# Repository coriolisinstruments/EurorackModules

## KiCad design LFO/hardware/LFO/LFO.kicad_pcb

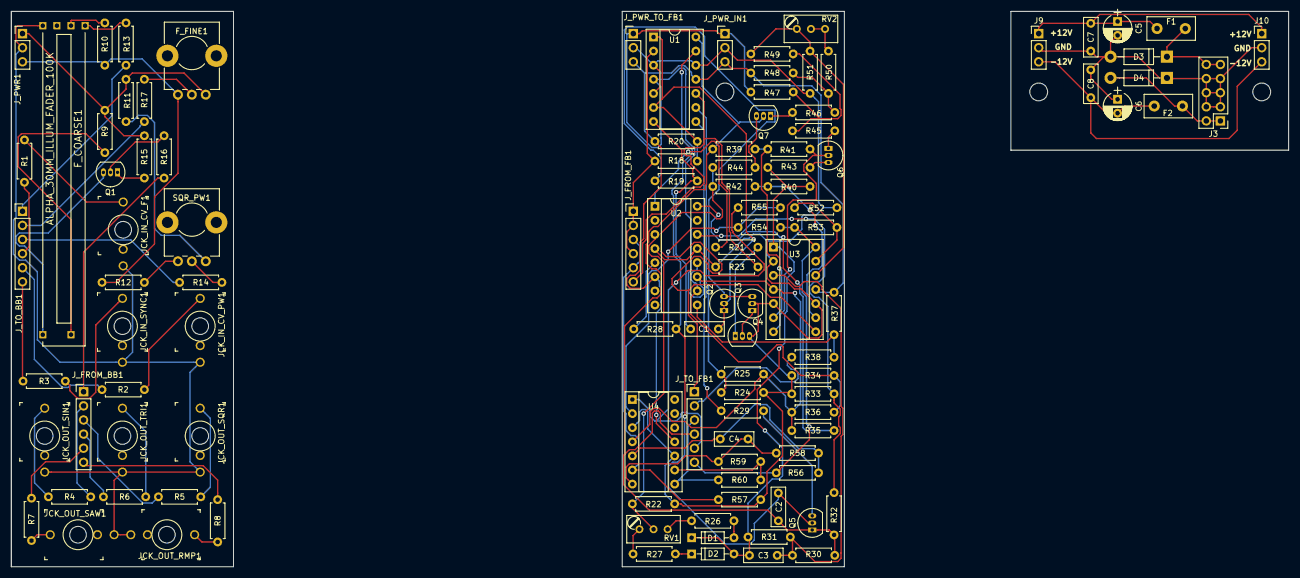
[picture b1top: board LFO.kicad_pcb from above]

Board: 2 copper layers, 230.0 x 100.0 mm, 111 parts (0 on the bottom side), 88 nets.

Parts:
C1: 100pF; C_Rect_L7.0mm_W2.5mm_P5.00mm
C2: 0.02uF; C_Rect_L7.0mm_W2.5mm_P5.00mm
C3, C4: 10pF; C_Rect_L7.0mm_W2.5mm_P5.00mm
C5, C6: 10uF; CP_Radial_D5.0mm_P2.50mm
C7, C8: 100nF; C_Rect_L7.0mm_W2.5mm_P5.00mm
D1, D2: 1N4148; D_DO-35_SOD27_P7.62mm_Horizontal
D3, D4: 1N4001; D_DO-41_SOD81_P10.16mm_Horizontal
F1, F2: Polyfuse; Fuse_TE5_Littlefuse-395Series
F_COARSE1: ALPHA_30MM_ILLUM_FADER_100K; ALPHA_ILL_FADER_45MM
F_FINE1: 100K; Potentiometer_Alps_RK09K_Horizontal
J3: Conn_02x05_Odd_Even; Pin_Header_Straight_2x05_Pitch2.54mm
J9, J10: Conn_01x03_Male; Pin_Header_Straight_1x03_Pitch2.54mm
JCK_IN_CV_F1: THONKICONNNEW; WQP-PJ301M-12_JACK
JCK_IN_CV_PW1: THONKICONNNEW; WQP-PJ301M-12_JACK
JCK_IN_SYNC1: THONKICONNNEW; WQP-PJ301M-12_JACK
JCK_OUT_RMP1: THONKICONNNEW; WQP-PJ301M-12_JACK
JCK_OUT_SAW1: THONKICONNNEW; WQP-PJ301M-12_JACK
JCK_OUT_SIN1: THONKICONNNEW; WQP-PJ301M-12_JACK
JCK_OUT_SQR1: THONKICONNNEW; WQP-PJ301M-12_JACK
JCK_OUT_TRI1: THONKICONNNEW; WQP-PJ301M-12_JACK
J_FROM_BB1: Conn_01x06_Male; Pin_Header_Straight_1x06_Pitch2.54mm
J_FROM_FB1: Conn_01x06_Female; Pin_Header_Straight_1x06_Pitch2.54mm
J_PWR1: Conn_01x03_Male; Pin_Header_Straight_1x03_Pitch2.54mm
J_PWR_IN1: Conn_01x03_Male; Pin_Header_Straight_1x03_Pitch2.54mm
J_PWR_TO_FB1: Conn_01x03_Female; Pin_Header_Straight_1x03_Pitch2.54mm
J_TO_BB1: Conn_01x06_Male; Pin_Header_Straight_1x06_Pitch2.54mm
J_TO_FB1: Conn_01x06_Female; Pin_Header_Straight_1x06_Pitch2.54mm
Q1, Q2, Q3: BC547; TO-92_Inline_Narrow_Oval
Q4: BC557; TO-92_Inline_Narrow_Oval
Q5, Q6, Q7: MPF102; TO-92_Inline_Narrow_Oval
R1, R3, R11, R12, R13, R16, R23, R25, R26, R27, R29, R53, R56: 100K; R_Axial_DIN0207_L6.3mm_D2.5mm_P7.62mm_Horizontal
R2, R14, R19, R21, R24, R45, R46, R49, R51, R54, R55, R60: 10K; R_Axial_DIN0207_L6.3mm_D2.5mm_P7.62mm_Horizontal
R4, R5, R6, R7, R8, R22, R38: 1K; R_Axial_DIN0207_L6.3mm_D2.5mm_P7.62mm_Horizontal
R9, R10, R59: 27K; R_Axial_DIN0207_L6.3mm_D2.5mm_P7.62mm_Horizontal
R15, R18, R33: 2K; R_Axial_DIN0207_L6.3mm_D2.5mm_P7.62mm_Horizontal
R17: 3M; R_Axial_DIN0207_L6.3mm_D2.5mm_P7.62mm_Horizontal
R20, R58: 4.7M; R_Axial_DIN0207_L6.3mm_D2.5mm_P7.62mm_Horizontal
R28: 39K; R_Axial_DIN0207_L6.3mm_D2.5mm_P7.62mm_Horizontal
R30: 120K; R_Axial_DIN0207_L6.3mm_D2.5mm_P7.62mm_Horizontal
R31: 270K; R_Axial_DIN0207_L6.3mm_D2.5mm_P7.62mm_Horizontal
R32: 110K; R_Axial_DIN0207_L6.3mm_D2.5mm_P7.62mm_Horizontal
R34: 180K; R_Axial_DIN0207_L6.3mm_D2.5mm_P7.62mm_Horizontal
R35: 680K; R_Axial_DIN0207_L6.3mm_D2.5mm_P7.62mm_Horizontal
R36: 2M; R_Axial_DIN0207_L6.3mm_D2.5mm_P7.62mm_Horizontal
R37: 4.7K; R_Axial_DIN0207_L6.3mm_D2.5mm_P7.62mm_Horizontal
R39, R41: 20K; R_Axial_DIN0207_L6.3mm_D2.5mm_P7.62mm_Horizontal
R40, R42, R52: 47K; R_Axial_DIN0207_L6.3mm_D2.5mm_P7.62mm_Horizontal
R43, R44: 30K; R_Axial_DIN0207_L6.3mm_D2.5mm_P7.62mm_Horizontal
R47, R48: 15K; R_Axial_DIN0207_L6.3mm_D2.5mm_P7.62mm_Horizontal
R50: 9.1K; R_Axial_DIN0207_L6.3mm_D2.5mm_P7.62mm_Horizontal
R57: 1M; R_Axial_DIN0207_L6.3mm_D2.5mm_P7.62mm_Horizontal
RV1: 100K; Potentiometer_Trimmer_Bourns_3296W
RV2: 2K; Potentiometer_Trimmer_Bourns_3296W
SQR_PW1: 100K; Potentiometer_Alps_RK09K_Horizontal
U1, U3, U4: TL074; DIP-14_W7.62mm_Socket
U2: LM13700; DIP-16_W7.62mm_Socket
screw: MountingHole_3.2mm_M3
screw#2, screw#3: MountingHole_3.2mm_M3

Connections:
+12V: J_PWR_IN1.1, J_PWR_TO_FB1.1, R25.2, R35.2, R36.2, R47.2, U1.4, U2.11, U3.4, U4.4
/LFO back board/-12V: J_PWR_IN1.3, J_PWR_TO_FB1.3, R20.1, R37.1, R48.1, U1.11, U2.6, U3.11, U4.11
/LFO back board/GND: J_PWR_IN1.2, J_PWR_TO_FB1.2, Q3.2, Q4.3, R22.1, R23.1, R24.1, R33.1, R34.1, R51.1, R52.2, R57.2, U1.3, U1.5, U1.12, U2.4, U2.13, U3.2, U3.5, U3.10, U4.3, U4.10
/LFO back board/Integrator/BIAS_INPUT: R21.1, U2.1
/LFO back board/Integrator/SQR_RAW: C3.1, D1.1, D2.2, R31.1, R40.2, R43.2, U3.1
/LFO back board/LED_RATE: J_TO_FB1.1, R42.1, R44.2, U3.8
/LFO back board/RMP: J_TO_FB1.6, R53.1, R54.2, R56.2, U3.14
/LFO back board/SAW: J_TO_FB1.5, R55.1, U4.1
/LFO back board/SIN: J_TO_FB1.2, R38.1
/LFO back board/SQR: J_TO_FB1.3, R60.1, U4.8
/LFO back board/TRI: C2.1, J_TO_FB1.4, Q5.1, Q7.2, R30.2, R32.2, R39.2, U1.14
/LFO back board/V_CF: J_FROM_FB1.1, J_FROM_FB1.2, J_FROM_FB1.4, R18.2, U1.2
/LFO back board/V_CV_PW: J_FROM_FB1.3, J_FROM_FB1.5, R57.1, U4.6
/LFO back board/V_SYNC: J_FROM_FB1.6, R23.2, U1.10
/LFO front board/+12V_FB: F_FINE1.1, J_PWR1.1, R9.1, R11.2, R15.2
/LFO front board/-12V_FB: F_FINE1.3, J_PWR1.3, R10.2, R12.2
/LFO front board/GND_FB: F_COARSE1.E, JCK_IN_CV_F1.P$3_SLEEVE, JCK_IN_CV_PW1.P$3_SLEEVE, JCK_IN_SYNC1.P$3_SLEEVE, JCK_OUT_RMP1.P$3_SLEEVE, JCK_OUT_SAW1.P$3_SLEEVE, JCK_OUT_SIN1.P$3_SLEEVE, JCK_OUT_SQR1.P$3_SLEEVE, JCK_OUT_TRI1.P$3_SLEEVE, J_PWR1.2
/LFO front board/LED_RATE_FB: J_FROM_BB1.1, R16.2
/LFO front board/RMP_FB: J_FROM_BB1.6, R8.1
/LFO front board/SAW_FB: J_FROM_BB1.5, R7.1
/LFO front board/SIN_FB: J_FROM_BB1.2, R4.1
/LFO front board/SQR_FB: J_FROM_BB1.3, R5.1
/LFO front board/TRI_FB: J_FROM_BB1.4, R6.1
/LFO front board/V_CF_FB: J_TO_BB1.1, R13.1
/LFO front board/V_CV_F_FB: J_TO_BB1.4, R1.1
/LFO front board/V_CV_PW_FB: J_TO_BB1.5, R2.1
/LFO front board/V_FF_FB: J_TO_BB1.2, R17.1
/LFO front board/V_PW_FB: J_TO_BB1.3, R14.2
/LFO front board/V_SYNC_FB: J_TO_BB1.6, R3.1
unnamed: C1.1, R19.2, U1.7
unnamed: C1.2, Q2.1, Q2.2, R18.1, R20.2, U1.1, U1.6
unnamed: C2.2, Q5.2, R28.1, U1.13
unnamed: C3.2, R30.1, R31.2, U3.3
unnamed: C4.1, R58.1, R59.2, U4.7
unnamed: C4.2, R56.1, R58.2, U4.5
unnamed: C5.1, C7.1, F1.1, J9.1, J10.1
unnamed: C5.2, C6.1, C7.2, C8.1, D3.2, D4.1, J3.3, J3.4, J3.5, J3.6, J3.7, J3.8, J9.2, J10.2
unnamed: C6.2, C8.2, F2.2, J9.3, J10.3
unnamed: D1.2, R26.1
unnamed: D2.1, R27.1
unnamed: D3.1, F1.2, J3.9, J3.10
unnamed: D4.2, F2.1, J3.1, J3.2
unnamed: F_COARSE1.1, R10.1
unnamed: F_COARSE1.2, R13.2
unnamed: F_COARSE1.3, R9.2
unnamed: F_COARSE1.B, Q1.3
unnamed: F_FINE1.2, R17.2
unnamed: JCK_IN_CV_F1.P$1_TIP, R1.2
unnamed: JCK_IN_CV_PW1.P$1_TIP, R2.2
unnamed: JCK_IN_SYNC1.P$1_TIP, R3.2
unnamed: JCK_OUT_RMP1.P$1_TIP, R8.2
unnamed: JCK_OUT_SAW1.P$1_TIP, R7.2
unnamed: JCK_OUT_SIN1.P$1_TIP, R4.2
unnamed: JCK_OUT_SQR1.P$1_TIP, R5.2
unnamed: JCK_OUT_TRI1.P$1_TIP, R6.2
unnamed: Q1.1, R15.1
unnamed: Q1.2, R16.1
unnamed: Q2.3, Q3.3, R19.1
unnamed: Q3.1, Q4.2
unnamed: Q4.1, R21.2
unnamed: Q5.3, R29.2
unnamed: Q6.1, R45.2
unnamed: Q6.2, R41.1, U3.7
unnamed: Q6.3, R43.1
unnamed: Q7.1, R46.2
unnamed: Q7.3, R44.1
unnamed: R11.1, SQR_PW1.1
unnamed: R12.1, SQR_PW1.3
unnamed: R14.1, SQR_PW1.2
unnamed: R22.2, RV1.2, U2.3
unnamed: R24.2, R25.1, U1.9
unnamed: R26.2, RV1.3
unnamed: R27.2, RV1.1
unnamed: R28.2, U2.5
unnamed: R29.1, U1.8
unnamed: R32.1, R33.2, U2.14
unnamed: R34.2, R36.1, U2.10, U2.12
unnamed: R35.1, U2.16
unnamed: R37.2, R38.2, U2.9
unnamed: R39.1, R41.2, U3.6
unnamed: R40.1, R42.2, U3.9
unnamed: R45.1, R47.1, R49.2
unnamed: R46.1, R48.2, R50.2
unnamed: R49.1, R51.2, RV2.1, U3.12
unnamed: R50.1, RV2.2, RV2.3
unnamed: R52.1, R53.2, U3.13
unnamed: R54.1, R55.2, U4.2
unnamed: R59.1, R60.2, U4.9

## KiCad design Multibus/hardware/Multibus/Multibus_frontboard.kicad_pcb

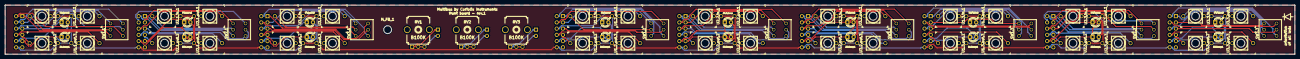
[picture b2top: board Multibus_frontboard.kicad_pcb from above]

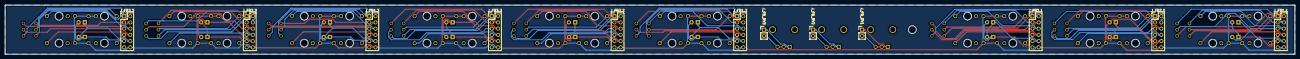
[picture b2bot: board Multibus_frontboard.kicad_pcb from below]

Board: 2 copper layers, 526.0 x 20.0 mm, 79 parts (12 on the bottom side), 106 nets.

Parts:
D1.1.neg.1, D1.1.pos.1, D1.2.neg.1, D1.2.pos.1, D1.3.neg.1, D1.3.pos.1, D2.1.neg.1, D2.1.pos.1, D2.2.neg.1, D2.2.pos.1, D2.3.neg.1, D2.3.pos.1, D3.1.neg.1, D3.1.pos.1, D3.2.neg.1, D3.2.pos.1, D3.3.neg.1, D3.3.pos.1: LED; LED_D3.0mm_smalltext
H_FB_1: MountingHole; MountingHole_3.2mm_M3
J_FB1.1, J_FB1.2, J_FB1.3, J_FB2.1, J_FB2.2, J_FB2.3, J_FB3.1, J_FB3.2, J_FB3.3: Conn_01x12; PinHeader_2x06_P2.54mm_Vertical
J_FB_RV1, J_FB_RV2, J_FB_RV3: Conn_01x02; PinHeader_1x02_P2.54mm_Vertical
RV1, RV2, RV3: B100K; 9MM_SNAP-IN_POT
SW1.1, SW1.2, SW1.3, SW2.1, SW2.2, SW2.3, SW3.1, SW3.2, SW3.3: SW_DPDT_x2; SUBMINI_TOGGLE_DPDT
U1.1.in.1, U1.1.out.1, U1.1.out.2, U1.1.out.3, U1.2.in.1, U1.2.out.1, U1.2.out.2, U1.2.out.3, U1.3.in.1, U1.3.out.1, U1.3.out.2, U1.3.out.3, U2.1.in.1, U2.1.out.1, U2.1.out.2, U2.1.out.3, U2.2.in.1, U2.2.out.1, U2.2.out.2, U2.2.out.3, U2.3.in.1, U2.3.out.1, U2.3.out.2, U2.3.out.3, U3.1.in.1, U3.1.out.1, U3.1.out.2, U3.1.out.3, U3.2.in.1, U3.2.out.1, U3.2.out.2, U3.2.out.3, U3.3.in.1, U3.3.out.1, U3.3.out.2, U3.3.out.3: THONKICONNNEW; MusicThingModular-WQP-PJ301M-12_JACK

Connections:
/cv_bus1/fb.1.1.leds.in: D1.1.neg.1.1, D1.1.pos.1.2, J_FB1.1.9
/cv_bus1/fb.1.1.leds.out: D1.1.neg.1.2, D1.1.pos.1.1, J_FB1.1.10
/cv_bus1/fb.1.1.out.1: J_FB1.1.6, U1.1.out.1.P$1_TIP
/cv_bus1/fb.1.1.out.2: J_FB1.1.7, U1.1.out.2.P$1_TIP
/cv_bus1/fb.1.1.out.3: J_FB1.1.8, U1.1.out.3.P$1_TIP
/cv_bus1/fb.1.2.leds.in: D1.2.neg.1.1, D1.2.pos.1.2, J_FB1.2.9
/cv_bus1/fb.1.2.leds.out: D1.2.neg.1.2, D1.2.pos.1.1, J_FB1.2.10
/cv_bus1/fb.1.2.out.1: J_FB1.2.6, U1.2.out.1.P$1_TIP
/cv_bus1/fb.1.2.out.2: J_FB1.2.7, U1.2.out.2.P$1_TIP
/cv_bus1/fb.1.2.out.3: J_FB1.2.8, U1.2.out.3.P$1_TIP
/cv_bus1/fb.1.3.leds.in: D1.3.neg.1.1, D1.3.pos.1.2, J_FB1.3.9
/cv_bus1/fb.1.3.leds.out: D1.3.neg.1.2, D1.3.pos.1.1, J_FB1.3.10
/cv_bus1/fb.1.3.out.1: J_FB1.3.6, U1.3.out.1.P$1_TIP
/cv_bus1/fb.1.3.out.2: J_FB1.3.7, U1.3.out.2.P$1_TIP
/cv_bus1/fb.1.3.out.3: J_FB1.3.8, U1.3.out.3.P$1_TIP
/cv_bus1/fb.bus1.1.in: J_FB1.1.3, SW1.1.3
/cv_bus1/fb.bus1.1.out: J_FB1.1.4, SW1.1.6
/cv_bus1/fb.bus1.2.in: J_FB1.2.3, SW1.2.3
/cv_bus1/fb.bus1.2.out: J_FB1.2.4, SW1.2.6
/cv_bus1/fb.bus1.3.in: J_FB1.3.3, SW1.3.3
/cv_bus1/fb.bus1.3.out: J_FB1.3.4, SW1.3.6
/cv_bus1/fb.rv1.in: J_FB_RV1.1, RV1.1
/cv_bus1/fb.rv1.out: J_FB_RV1.2, RV1.2, RV1.3
/cv_bus1/fb.sel.1.1.out: J_FB1.1.5, SW1.1.5
/cv_bus1/fb.sel.1.2.out: J_FB1.2.5, SW1.2.5
/cv_bus1/fb.sel.1.3.out: J_FB1.3.5, SW1.3.5
/cv_bus1/fb.solo1.1.in: J_FB1.1.1, SW1.1.1
/cv_bus1/fb.solo1.1.out: J_FB1.1.2, SW1.1.4
/cv_bus1/fb.solo1.2.in: J_FB1.2.1, SW1.2.1
/cv_bus1/fb.solo1.2.out: J_FB1.2.2, SW1.2.4
/cv_bus1/fb.solo1.3.in: J_FB1.3.1, SW1.3.1
/cv_bus1/fb.solo1.3.out: J_FB1.3.2, SW1.3.4
/cv_bus2/fb.2.1.leds.in: D2.1.neg.1.1, D2.1.pos.1.2, J_FB2.1.9
/cv_bus2/fb.2.1.leds.out: D2.1.neg.1.2, D2.1.pos.1.1, J_FB2.1.10
/cv_bus2/fb.2.1.out.1: J_FB2.1.6, U2.1.out.1.P$1_TIP
/cv_bus2/fb.2.1.out.2: J_FB2.1.7, U2.1.out.2.P$1_TIP
/cv_bus2/fb.2.1.out.3: J_FB2.1.8, U2.1.out.3.P$1_TIP
/cv_bus2/fb.2.2.leds.in: D2.2.neg.1.1, D2.2.pos.1.2, J_FB2.2.9
/cv_bus2/fb.2.2.leds.out: D2.2.neg.1.2, D2.2.pos.1.1, J_FB2.2.10
/cv_bus2/fb.2.2.out.1: J_FB2.2.6, U2.2.out.1.P$1_TIP
/cv_bus2/fb.2.2.out.2: J_FB2.2.7, U2.2.out.2.P$1_TIP
/cv_bus2/fb.2.2.out.3: J_FB2.2.8, U2.2.out.3.P$1_TIP
/cv_bus2/fb.2.3.leds.in: D2.3.neg.1.1, D2.3.pos.1.2, J_FB2.3.9
/cv_bus2/fb.2.3.leds.out: D2.3.neg.1.2, D2.3.pos.1.1, J_FB2.3.10
/cv_bus2/fb.2.3.out.1: J_FB2.3.6, U2.3.out.1.P$1_TIP
/cv_bus2/fb.2.3.out.2: J_FB2.3.7, U2.3.out.2.P$1_TIP
/cv_bus2/fb.2.3.out.3: J_FB2.3.8, U2.3.out.3.P$1_TIP
/cv_bus2/fb.bus2.1.in: J_FB2.1.3, SW2.1.3
/cv_bus2/fb.bus2.1.out: J_FB2.1.4, SW2.1.6
/cv_bus2/fb.bus2.2.in: J_FB2.2.3, SW2.2.3
/cv_bus2/fb.bus2.2.out: J_FB2.2.4, SW2.2.6
/cv_bus2/fb.bus2.3.in: J_FB2.3.3, SW2.3.3
/cv_bus2/fb.bus2.3.out: J_FB2.3.4, SW2.3.6
/cv_bus2/fb.rv2.in: J_FB_RV2.1, RV2.1
/cv_bus2/fb.rv2.out: J_FB_RV2.2, RV2.2, RV2.3
/cv_bus2/fb.sel.2.1.out: J_FB2.1.5, SW2.1.5
/cv_bus2/fb.sel.2.2.out: J_FB2.2.5, SW2.2.5
/cv_bus2/fb.sel.2.3.out: J_FB2.3.5, SW2.3.5
/cv_bus2/fb.solo2.1.in: J_FB2.1.1, SW2.1.1
/cv_bus2/fb.solo2.1.out: J_FB2.1.2, SW2.1.4
/cv_bus2/fb.solo2.2.in: J_FB2.2.1, SW2.2.1
/cv_bus2/fb.solo2.2.out: J_FB2.2.2, SW2.2.4
/cv_bus2/fb.solo2.3.in: J_FB2.3.1, SW2.3.1
/cv_bus2/fb.solo2.3.out: J_FB2.3.2, SW2.3.4
/cv_bus3/fb.3.1.leds.in: D3.1.neg.1.1, D3.1.pos.1.2, J_FB3.1.9
/cv_bus3/fb.3.1.leds.out: D3.1.neg.1.2, D3.1.pos.1.1, J_FB3.1.10
/cv_bus3/fb.3.1.out.1: J_FB3.1.6, U3.1.out.1.P$1_TIP
/cv_bus3/fb.3.1.out.2: J_FB3.1.7, U3.1.out.2.P$1_TIP
/cv_bus3/fb.3.1.out.3: J_FB3.1.8, U3.1.out.3.P$1_TIP
/cv_bus3/fb.3.2.leds.in: D3.2.neg.1.1, D3.2.pos.1.2, J_FB3.2.9
/cv_bus3/fb.3.2.leds.out: D3.2.neg.1.2, D3.2.pos.1.1, J_FB3.2.10
/cv_bus3/fb.3.2.out.1: J_FB3.2.6, U3.2.out.1.P$1_TIP
/cv_bus3/fb.3.2.out.2: J_FB3.2.7, U3.2.out.2.P$1_TIP
/cv_bus3/fb.3.2.out.3: J_FB3.2.8, U3.2.out.3.P$1_TIP
/cv_bus3/fb.3.3.leds.in: D3.3.neg.1.1, D3.3.pos.1.2, J_FB3.3.9
/cv_bus3/fb.3.3.leds.out: D3.3.neg.1.2, D3.3.pos.1.1, J_FB3.3.10
/cv_bus3/fb.3.3.out.1: J_FB3.3.6, U3.3.out.1.P$1_TIP
/cv_bus3/fb.3.3.out.2: J_FB3.3.7, U3.3.out.2.P$1_TIP
/cv_bus3/fb.3.3.out.3: J_FB3.3.8, U3.3.out.3.P$1_TIP
/cv_bus3/fb.bus3.1.in: J_FB3.1.3, SW3.1.3
/cv_bus3/fb.bus3.1.out: J_FB3.1.4, SW3.1.6
/cv_bus3/fb.bus3.2.in: J_FB3.2.3, SW3.2.3
/cv_bus3/fb.bus3.2.out: J_FB3.2.4, SW3.2.6
/cv_bus3/fb.bus3.3.in: J_FB3.3.3, SW3.3.3
/cv_bus3/fb.bus3.3.out: J_FB3.3.4, SW3.3.6
/cv_bus3/fb.rv3.in: J_FB_RV3.1, RV3.1
/cv_bus3/fb.rv3.out: J_FB_RV3.2, RV3.2, RV3.3
/cv_bus3/fb.sel.3.1.out: J_FB3.1.5, SW3.1.5
/cv_bus3/fb.sel.3.2.out: J_FB3.2.5, SW3.2.5
/cv_bus3/fb.sel.3.3.out: J_FB3.3.5, SW3.3.5
/cv_bus3/fb.solo3.1.in: J_FB3.1.1, SW3.1.1
/cv_bus3/fb.solo3.1.out: J_FB3.1.2, SW3.1.4
/cv_bus3/fb.solo3.2.in: J_FB3.2.1, SW3.2.1
/cv_bus3/fb.solo3.2.out: J_FB3.2.2, SW3.2.4
/cv_bus3/fb.solo3.3.in: J_FB3.3.1, SW3.3.1
/cv_bus3/fb.solo3.3.out: J_FB3.3.2, SW3.3.4
FB_GND: J_FB1.1.12, J_FB1.2.12, J_FB1.3.12, J_FB2.1.12, J_FB2.2.12, J_FB2.3.12, J_FB3.1.12, J_FB3.2.12, J_FB3.3.12, U1.1.in.1.P$2_SWITCH, U1.1.in.1.P$3_SLEEVE, U1.1.out.1.P$3_SLEEVE, U1.1.out.2.P$3_SLEEVE, U1.1.out.3.P$3_SLEEVE, U1.2.in.1.P$2_SWITCH, U1.2.in.1.P$3_SLEEVE, U1.2.out.1.P$3_SLEEVE, U1.2.out.2.P$3_SLEEVE, U1.2.out.3.P$3_SLEEVE, U1.3.in.1.P$2_SWITCH, U1.3.in.1.P$3_SLEEVE, U1.3.out.1.P$3_SLEEVE, U1.3.out.2.P$3_SLEEVE, U1.3.out.3.P$3_SLEEVE, U2.1.in.1.P$2_SWITCH, U2.1.in.1.P$3_SLEEVE, U2.1.out.1.P$3_SLEEVE, U2.1.out.2.P$3_SLEEVE, U2.1.out.3.P$3_SLEEVE, U2.2.in.1.P$2_SWITCH, U2.2.in.1.P$3_SLEEVE, U2.2.out.1.P$3_SLEEVE, U2.2.out.2.P$3_SLEEVE, U2.2.out.3.P$3_SLEEVE, U2.3.in.1.P$2_SWITCH, U2.3.in.1.P$3_SLEEVE, U2.3.out.1.P$3_SLEEVE, U2.3.out.2.P$3_SLEEVE, U2.3.out.3.P$3_SLEEVE, U3.1.in.1.P$2_SWITCH, U3.1.in.1.P$3_SLEEVE, U3.1.out.1.P$3_SLEEVE, U3.1.out.2.P$3_SLEEVE, U3.1.out.3.P$3_SLEEVE, U3.2.in.1.P$2_SWITCH, U3.2.in.1.P$3_SLEEVE, U3.2.out.1.P$3_SLEEVE, U3.2.out.2.P$3_SLEEVE, U3.2.out.3.P$3_SLEEVE, U3.3.in.1.P$2_SWITCH, U3.3.in.1.P$3_SLEEVE, U3.3.out.1.P$3_SLEEVE, U3.3.out.2.P$3_SLEEVE, U3.3.out.3.P$3_SLEEVE
unnamed: SW1.1.2, U1.1.in.1.P$1_TIP
unnamed: SW1.2.2, U1.2.in.1.P$1_TIP
unnamed: SW1.3.2, U1.3.in.1.P$1_TIP
unnamed: SW2.1.2, U2.1.in.1.P$1_TIP
unnamed: SW2.2.2, U2.2.in.1.P$1_TIP
unnamed: SW2.3.2, U2.3.in.1.P$1_TIP
unnamed: SW3.1.2, U3.1.in.1.P$1_TIP
unnamed: SW3.2.2, U3.2.in.1.P$1_TIP
unnamed: SW3.3.2, U3.3.in.1.P$1_TIP

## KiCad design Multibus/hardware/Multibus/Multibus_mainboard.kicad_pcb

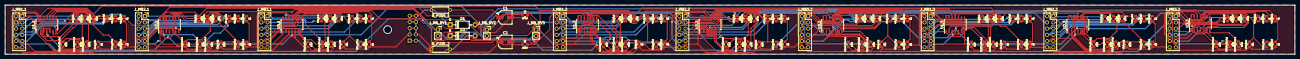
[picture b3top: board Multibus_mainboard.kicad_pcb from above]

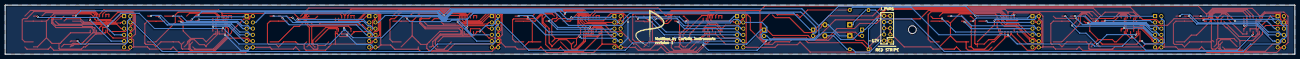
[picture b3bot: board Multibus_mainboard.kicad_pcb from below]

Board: 2 copper layers, 526.0 x 20.0 mm, 140 parts (2 on the bottom side), 125 nets.

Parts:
C1, C2: 10uF (25V); CP_Elec_5x5.8
C1.1.feedback.1, C1.2.feedback.1, C1.3.feedback.1, C2.1.feedback.1, C2.2.feedback.1, C2.3.feedback.1, C3.1.feedback.1, C3.2.feedback.1, C3.3.feedback.1: 10pF; C_0805_2012Metric_Pad1.15x1.40mm_HandSolder_smalltext
C3, C4: 100nF; C_0805_2012Metric_Pad1.15x1.40mm_HandSolder_smalltext
D1, D2: IN4001; D_DO-41_SOD81_P10.16mm_Horizontal
H_MB_2: MountingHole; MountingHole_3.2mm_M3
J_MB1.1, J_MB1.2, J_MB1.3, J_MB2.1, J_MB2.2, J_MB2.3, J_MB3.1, J_MB3.2, J_MB3.3: Conn_01x12; PinSocket_2x06_P2.54mm_Vertical
J_MB_RV1, J_MB_RV2, J_MB_RV3: Conn_01x02; PinSocket_1x02_P2.54mm_Vertical
J_PWR1: Conn_02x05_Odd_Even; PinHeader_2x05_P2.54mm_Vertical
MK1: CoriolisLogo; art_Coriolis_logo_fsilk
R1.1.feedback.1, R1.1.feedback.2, R1.1.in.1, R1.1.in.2, R1.1.in.3, R1.2.feedback.1, R1.2.feedback.2, R1.2.in.1, R1.2.in.2, R1.2.in.3, R1.3.feedback.1, R1.3.feedback.2, R1.3.in.1, R1.3.in.2, R1.3.in.3, R2.1.feedback.1, R2.1.feedback.2, R2.1.in.1, R2.1.in.2, R2.1.in.3, R2.2.feedback.1, R2.2.feedback.2, R2.2.in.1, R2.2.in.2, R2.2.in.3, R2.3.feedback.1, R2.3.feedback.2, R2.3.in.1, R2.3.in.2, R2.3.in.3, R3.1.feedback.1, R3.1.feedback.2, R3.1.in.1, R3.1.in.2, R3.1.in.3, R3.2.feedback.1, R3.2.feedback.2, R3.2.in.1, R3.2.in.2, R3.2.in.3, R3.3.feedback.1, R3.3.feedback.2, R3.3.in.1, R3.3.in.2, R3.3.in.3: 100K; R_0805_2012Metric_Pad1.15x1.40mm_HandSolder_smalltext
R1.1.led.1, R1.1.split.2, R1.2.led.1, R1.2.split.2, R1.3.led.1, R1.3.split.2, R2.1.split.2, R2.2.split.2, R2.3.split.2, R3.1.split.2, R3.2.split.2, R3.3.split.2: 1K; R_0805_2012Metric_Pad1.15x1.40mm_HandSolder_smalltext
R1.1.out.1, R1.1.out.2, R1.1.out.3, R1.2.out.1, R1.2.out.2, R1.2.out.3, R1.3.out.1, R1.3.out.2, R1.3.out.3, R2.1.out.1, R2.1.out.2, R2.1.out.3, R2.2.out.1, R2.2.out.2, R2.2.out.3, R2.3.out.1, R2.3.out.2, R2.3.out.3, R3.1.out.1, R3.1.out.2, R3.1.out.3, R3.2.out.1, R3.2.out.2, R3.2.out.3, R3.3.out.1, R3.3.out.2, R3.3.out.3: 51; R_0805_2012Metric_Pad1.15x1.40mm_HandSolder_smalltext
R1.1.split.1, R1.2.split.1, R1.3.split.1, R2.1.split.1, R2.2.split.1, R2.3.split.1, R3.1.split.1, R3.2.split.1, R3.3.split.1: 10K; R_0805_2012Metric_Pad1.15x1.40mm_HandSolder_smalltext
R2.1.led.1, R2.2.led.1, R2.3.led.1: 510R; R_0805_2012Metric_Pad1.15x1.40mm_HandSolder_smalltext
R3.1.led.1, R3.2.led.1, R3.3.led.1: 5K1; R_0805_2012Metric_Pad1.15x1.40mm_HandSolder_smalltext
R_FUSE_1, R_FUSE_2: 10R; R_Axial_DIN0207_L6.3mm_D2.5mm_P7.62mm_Horizontal
U1.1, U1.2, U1.3, U2.1, U2.2, U2.3, U3.1, U3.2, U3.3: TL074; SOIC-14_3.9x8.7mm_P1.27mm

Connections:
+12V: C1.1, C3.1, R_FUSE_1.1, U1.1.4, U1.2.4, U1.3.4, U2.1.4, U2.2.4, U2.3.4, U3.1.4, U3.2.4, U3.3.4
-12V: C2.2, C4.2, R_FUSE_2.1, U1.1.11, U1.2.11, U1.3.11, U2.1.11, U2.2.11, U2.3.11, U3.1.11, U3.2.11, U3.3.11
/cv_bus1/1.1.leds.in: J_MB1.1.9, U1.1.8
/cv_bus1/1.1.leds.out: C1.1.feedback.1.1, J_MB1.1.10, R1.1.feedback.2.2, R1.1.led.1.2, R1.1.out.1.1, R1.1.out.2.1, R1.1.out.3.1, R1.1.split.1.1, U1.1.7, U1.1.9
/cv_bus1/1.1.out.1: J_MB1.1.6, R1.1.out.1.2
/cv_bus1/1.1.out.2: J_MB1.1.7, R1.1.out.2.2
/cv_bus1/1.1.out.3: J_MB1.1.8, R1.1.out.3.2
/cv_bus1/1.2.leds.in: J_MB1.2.9, U1.2.8
/cv_bus1/1.2.leds.out: C1.2.feedback.1.1, J_MB1.2.10, R1.2.feedback.2.2, R1.2.led.1.2, R1.2.out.1.1, R1.2.out.2.1, R1.2.out.3.1, R1.2.split.1.1, U1.2.7, U1.2.9
/cv_bus1/1.2.out.1: J_MB1.2.6, R1.2.out.1.2
/cv_bus1/1.2.out.2: J_MB1.2.7, R1.2.out.2.2
/cv_bus1/1.2.out.3: J_MB1.2.8, R1.2.out.3.2
/cv_bus1/1.3.leds.in: J_MB1.3.9, U1.3.8
/cv_bus1/1.3.leds.out: C1.3.feedback.1.1, J_MB1.3.10, R1.3.feedback.2.2, R1.3.led.1.2, R1.3.out.1.1, R1.3.out.2.1, R1.3.out.3.1, R1.3.split.1.1, U1.3.7, U1.3.9
/cv_bus1/1.3.out.1: J_MB1.3.6, R1.3.out.1.2
/cv_bus1/1.3.out.2: J_MB1.3.7, R1.3.out.2.2
/cv_bus1/1.3.out.3: J_MB1.3.8, R1.3.out.3.2
/cv_bus1/bus1.1.in: J_MB1.1.3, R1.1.in.3.1
/cv_bus1/bus1.2.in: J_MB1.2.3, R1.2.in.3.1
/cv_bus1/bus1.3.in: J_MB1.3.3, R1.3.in.3.1
/cv_bus1/bus1.out: J_MB1.1.4, J_MB1.2.4, J_MB1.3.4, J_MB_RV1.1, U1.1.14
/cv_bus1/rv1.out: J_MB_RV1.2, R1.1.in.3.2, R1.2.in.3.2, R1.3.in.3.2, U1.1.13
/cv_bus1/sel.1.1.out: J_MB1.1.5, R1.1.in.2.1
/cv_bus1/sel.1.2.out: J_MB1.2.5, R1.2.in.2.1
/cv_bus1/sel.1.3.out: J_MB1.3.5, R1.3.in.2.1
/cv_bus1/solo1.1.in: J_MB1.1.1, R1.1.in.1.1
/cv_bus1/solo1.1.out: J_MB1.1.2, R1.1.feedback.1.2, U1.1.1
/cv_bus1/solo1.2.in: J_MB1.2.1, R1.2.in.1.1
/cv_bus1/solo1.2.out: J_MB1.2.2, R1.2.feedback.1.2, U1.2.1
/cv_bus1/solo1.3.in: J_MB1.3.1, R1.3.in.1.1
/cv_bus1/solo1.3.out: J_MB1.3.2, R1.3.feedback.1.2, U1.3.1
/cv_bus2/2.1.leds.in: J_MB2.1.9, U2.1.8
/cv_bus2/2.1.leds.out: C2.1.feedback.1.1, J_MB2.1.10, R2.1.feedback.2.2, R2.1.led.1.2, R2.1.out.1.1, R2.1.out.2.1, R2.1.out.3.1, R2.1.split.1.1, U2.1.7, U2.1.9
/cv_bus2/2.1.out.1: J_MB2.1.6, R2.1.out.1.2
/cv_bus2/2.1.out.2: J_MB2.1.7, R2.1.out.2.2
/cv_bus2/2.1.out.3: J_MB2.1.8, R2.1.out.3.2
/cv_bus2/2.2.leds.in: J_MB2.2.9, U2.2.8
/cv_bus2/2.2.leds.out: C2.2.feedback.1.1, J_MB2.2.10, R2.2.feedback.2.2, R2.2.led.1.2, R2.2.out.1.1, R2.2.out.2.1, R2.2.out.3.1, R2.2.split.1.1, U2.2.7, U2.2.9
/cv_bus2/2.2.out.1: J_MB2.2.6, R2.2.out.1.2
/cv_bus2/2.2.out.2: J_MB2.2.7, R2.2.out.2.2
/cv_bus2/2.2.out.3: J_MB2.2.8, R2.2.out.3.2
/cv_bus2/2.3.leds.in: J_MB2.3.9, U2.3.8
/cv_bus2/2.3.leds.out: C2.3.feedback.1.1, J_MB2.3.10, R2.3.feedback.2.2, R2.3.led.1.2, R2.3.out.1.1, R2.3.out.2.1, R2.3.out.3.1, R2.3.split.1.1, U2.3.7, U2.3.9
/cv_bus2/2.3.out.1: J_MB2.3.6, R2.3.out.1.2
/cv_bus2/2.3.out.2: J_MB2.3.7, R2.3.out.2.2
/cv_bus2/2.3.out.3: J_MB2.3.8, R2.3.out.3.2
/cv_bus2/bus2.1.in: J_MB2.1.3, R2.1.in.1.1
/cv_bus2/bus2.2.in: J_MB2.2.3, R2.2.in.1.1
/cv_bus2/bus2.3.in: J_MB2.3.3, R2.3.in.1.1
/cv_bus2/bus2.out: J_MB2.1.4, J_MB2.2.4, J_MB2.3.4, J_MB_RV2.1, U2.1.14
/cv_bus2/rv2.out: J_MB_RV2.2, R2.1.in.1.2, R2.2.in.1.2, R2.3.in.1.2, U2.1.13
/cv_bus2/sel.2.1.out: J_MB2.1.5, R2.1.in.3.1
/cv_bus2/sel.2.2.out: J_MB2.2.5, R2.2.in.3.1
/cv_bus2/sel.2.3.out: J_MB2.3.5, R2.3.in.3.1
/cv_bus2/solo2.1.in: J_MB2.1.1, R2.1.in.2.1
/cv_bus2/solo2.1.out: J_MB2.1.2, R2.1.feedback.1.2, U2.1.1
/cv_bus2/solo2.2.in: J_MB2.2.1, R2.2.in.2.1
/cv_bus2/solo2.2.out: J_MB2.2.2, R2.2.feedback.1.2, U2.2.1
/cv_bus2/solo2.3.in: J_MB2.3.1, R2.3.in.2.1
/cv_bus2/solo2.3.out: J_MB2.3.2, R2.3.feedback.1.2, U2.3.1
/cv_bus3/3.1.leds.in: J_MB3.1.9, U3.1.8
/cv_bus3/3.1.leds.out: C3.1.feedback.1.1, J_MB3.1.10, R3.1.feedback.2.2, R3.1.led.1.2, R3.1.out.1.1, R3.1.out.2.1, R3.1.out.3.1, R3.1.split.1.1, U3.1.7, U3.1.9
/cv_bus3/3.1.out.1: J_MB3.1.6, R3.1.out.1.2
/cv_bus3/3.1.out.2: J_MB3.1.7, R3.1.out.2.2
/cv_bus3/3.1.out.3: J_MB3.1.8, R3.1.out.3.2
/cv_bus3/3.2.leds.in: J_MB3.2.9, U3.2.8
/cv_bus3/3.2.leds.out: C3.2.feedback.1.1, J_MB3.2.10, R3.2.feedback.2.2, R3.2.led.1.2, R3.2.out.1.1, R3.2.out.2.1, R3.2.out.3.1, R3.2.split.1.1, U3.2.7, U3.2.9
/cv_bus3/3.2.out.1: J_MB3.2.6, R3.2.out.1.2
/cv_bus3/3.2.out.2: J_MB3.2.7, R3.2.out.2.2
/cv_bus3/3.2.out.3: J_MB3.2.8, R3.2.out.3.2
/cv_bus3/3.3.leds.in: J_MB3.3.9, U3.3.8
/cv_bus3/3.3.leds.out: C3.3.feedback.1.1, J_MB3.3.10, R3.3.feedback.2.2, R3.3.led.1.2, R3.3.out.1.1, R3.3.out.2.1, R3.3.out.3.1, R3.3.split.1.1, U3.3.7, U3.3.9
/cv_bus3/3.3.out.1: J_MB3.3.6, R3.3.out.1.2
/cv_bus3/3.3.out.2: J_MB3.3.7, R3.3.out.2.2
/cv_bus3/3.3.out.3: J_MB3.3.8, R3.3.out.3.2
/cv_bus3/bus3.1.in: J_MB3.1.3, R3.1.in.1.1
/cv_bus3/bus3.2.in: J_MB3.2.3, R3.2.in.1.1
/cv_bus3/bus3.3.in: J_MB3.3.3, R3.3.in.1.1
/cv_bus3/bus3.out: J_MB3.1.4, J_MB3.2.4, J_MB3.3.4, J_MB_RV3.1, U3.1.14
/cv_bus3/rv3.out: J_MB_RV3.2, R3.1.in.1.2, R3.2.in.1.2, R3.3.in.1.2, U3.1.13
/cv_bus3/sel.3.1.out: J_MB3.1.5, R3.1.in.3.1
/cv_bus3/sel.3.2.out: J_MB3.2.5, R3.2.in.3.1
/cv_bus3/sel.3.3.out: J_MB3.3.5, R3.3.in.3.1
/cv_bus3/solo3.1.in: J_MB3.1.1, R3.1.in.2.1
/cv_bus3/solo3.1.out: J_MB3.1.2, R3.1.feedback.1.2, U3.1.1
/cv_bus3/solo3.2.in: J_MB3.2.1, R3.2.in.2.1
/cv_bus3/solo3.2.out: J_MB3.2.2, R3.2.feedback.1.2, U3.2.1
/cv_bus3/solo3.3.in: J_MB3.3.1, R3.3.in.2.1
/cv_bus3/solo3.3.out: J_MB3.3.2, R3.3.feedback.1.2, U3.3.1
GND: C1.2, C2.1, C3.2, C4.1, D1.2, D2.1, J_MB1.1.12, J_MB1.2.12, J_MB1.3.12, J_MB2.1.12, J_MB2.2.12, J_MB2.3.12, J_MB3.1.12, J_MB3.2.12, J_MB3.3.12, J_PWR1.3, J_PWR1.4, J_PWR1.5, J_PWR1.6, J_PWR1.7, J_PWR1.8, R1.1.led.1.1, R1.1.split.2.1, R1.2.led.1.1, R1.2.split.2.1, R1.3.led.1.1, R1.3.split.2.1, R2.1.led.1.1, R2.1.split.2.1, R2.2.led.1.1, R2.2.split.2.1, R2.3.led.1.1, R2.3.split.2.1, R3.1.led.1.1, R3.1.split.2.1, R3.2.led.1.1, R3.2.split.2.1, R3.3.led.1.1, R3.3.split.2.1, U1.1.3, U1.1.5, U1.1.12, U1.2.3, U1.2.5, U1.2.12, U1.3.3, U1.3.5, U1.3.12, U2.1.3, U2.1.5, U2.1.12, U2.2.3, U2.2.5, U2.2.12, U2.3.3, U2.3.5, U2.3.12, U3.1.3, U3.1.5, U3.1.12, U3.2.3, U3.2.5, U3.2.12, U3.3.3, U3.3.5, U3.3.12
unnamed: C1.1.feedback.1.2, R1.1.feedback.2.1, R1.1.in.2.2, U1.1.6
unnamed: C1.2.feedback.1.2, R1.2.feedback.2.1, R1.2.in.2.2, U1.2.6
unnamed: C1.3.feedback.1.2, R1.3.feedback.2.1, R1.3.in.2.2, U1.3.6
unnamed: C2.1.feedback.1.2, R2.1.feedback.2.1, R2.1.in.3.2, U2.1.6
unnamed: C2.2.feedback.1.2, R2.2.feedback.2.1, R2.2.in.3.2, U2.2.6
unnamed: C2.3.feedback.1.2, R2.3.feedback.2.1, R2.3.in.3.2, U2.3.6
unnamed: C3.1.feedback.1.2, R3.1.feedback.2.1, R3.1.in.3.2, U3.1.6
unnamed: C3.2.feedback.1.2, R3.2.feedback.2.1, R3.2.in.3.2, U3.2.6
unnamed: C3.3.feedback.1.2, R3.3.feedback.2.1, R3.3.in.3.2, U3.3.6
unnamed: D1.1, J_PWR1.9, J_PWR1.10, R_FUSE_1.2
unnamed: D2.2, J_PWR1.1, J_PWR1.2, R_FUSE_2.2
unnamed: R1.1.feedback.1.1, R1.1.in.1.2, U1.1.2
unnamed: R1.1.split.1.2, R1.1.split.2.2, U1.1.10
unnamed: R1.2.feedback.1.1, R1.2.in.1.2, U1.2.2
unnamed: R1.2.split.1.2, R1.2.split.2.2, U1.2.10
unnamed: R1.3.feedback.1.1, R1.3.in.1.2, U1.3.2
unnamed: R1.3.split.1.2, R1.3.split.2.2, U1.3.10
unnamed: R2.1.feedback.1.1, R2.1.in.2.2, U2.1.2
unnamed: R2.1.split.1.2, R2.1.split.2.2, U2.1.10
unnamed: R2.2.feedback.1.1, R2.2.in.2.2, U2.2.2
unnamed: R2.2.split.1.2, R2.2.split.2.2, U2.2.10
unnamed: R2.3.feedback.1.1, R2.3.in.2.2, U2.3.2
unnamed: R2.3.split.1.2, R2.3.split.2.2, U2.3.10
unnamed: R3.1.feedback.1.1, R3.1.in.2.2, U3.1.2
unnamed: R3.1.split.1.2, R3.1.split.2.2, U3.1.10
unnamed: R3.2.feedback.1.1, R3.2.in.2.2, U3.2.2
unnamed: R3.2.split.1.2, R3.2.split.2.2, U3.2.10
unnamed: R3.3.feedback.1.1, R3.3.in.2.2, U3.3.2
unnamed: R3.3.split.1.2, R3.3.split.2.2, U3.3.10
unnamed: U1.2.13, U1.2.14
unnamed: U1.3.13, U1.3.14
unnamed: U2.2.13, U2.2.14
unnamed: U2.3.13, U2.3.14
unnamed: U3.2.13, U3.2.14
unnamed: U3.3.13, U3.3.14
